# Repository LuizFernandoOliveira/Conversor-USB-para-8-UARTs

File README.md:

# Conversor USB para 8 UARTs

## Descrição
Este circuito eletrônico permite realizar a comunicação serial simutânea de até 8 portas UART com um computador via USB. Esta PCB é ideal para aplicações de testes de comunicação simultânea de múltiplos sensores com um único PC.

---

## Descrições técnicas

- Interface USB: Dispositivo USB High-Speed de 480Mbps;
- Possui oito UARTs (UART0 até UART7) e até 11 pinos de GPIOs controlados via USB;
- Taxa de Transmissão (Baud Rate): Variável de 1200bps até 6Mbps;
- Alimentação Principal: Requer apenas 3.3V;
- Controle de Fluxo: Suporte completo a Hardware Flow Control (CTS e RTS);
- Buffering (FIFO):
  - RX FIFO: 2048 bytes por UART.
  - TX FIFO: 1024 bytes por UART.
- Configurações UART:
  - Bits de Dados: 8 bits;
  - Paridade: Ímpar, Par e Nenhuma;
  - Bits de Parada: 1 ou 2.

---

## Estrutura do repositório
Os arquivos de hardware foram desenvolvidos utilizando o KiCad 9.0.
- **`.kicad_pcb`**: Layout da placa de circuito impresso (Board).
- **`.kicad_sch`**: Esquemático eletrônico do sistema (Schematic).
- **`.kicad_pro`**: Gerenciador de projeto do KiCad (Project).

---

## Autor
**Dr. Luiz Fernando Pinto de Oliveira**

*Engenheiro Eletrônico especializado em Sistemas Embarcados e Ultra-Low Power.*
- **Website:** [FAPLO](https://faplo.webnode.page/)
- **LinkedIn:** [lfpo](https://www.linkedin.com/in/lfpo/)

---

Shield: [![CC BY-NC-ND 4.0][cc-by-nc-nd-shield]][cc-by-nc-nd]

This work is licensed under a
[Creative Commons Attribution-NonCommercial-NoDerivs 4.0 International License][cc-by-nc-nd].

[![CC BY-NC-ND 4.0][cc-by-nc-nd-image]][cc-by-nc-nd]

[cc-by-nc-nd]: http://creativecommons.org/licenses/by-nc-nd/4.0/
[cc-by-nc-nd-image]: https://licensebuttons.net/l/by-nc-nd/4.0/88x31.png
[cc-by-nc-nd-shield]: https://img.shields.io/badge/License-CC%20BY--NC--ND%204.0-lightgrey.svg

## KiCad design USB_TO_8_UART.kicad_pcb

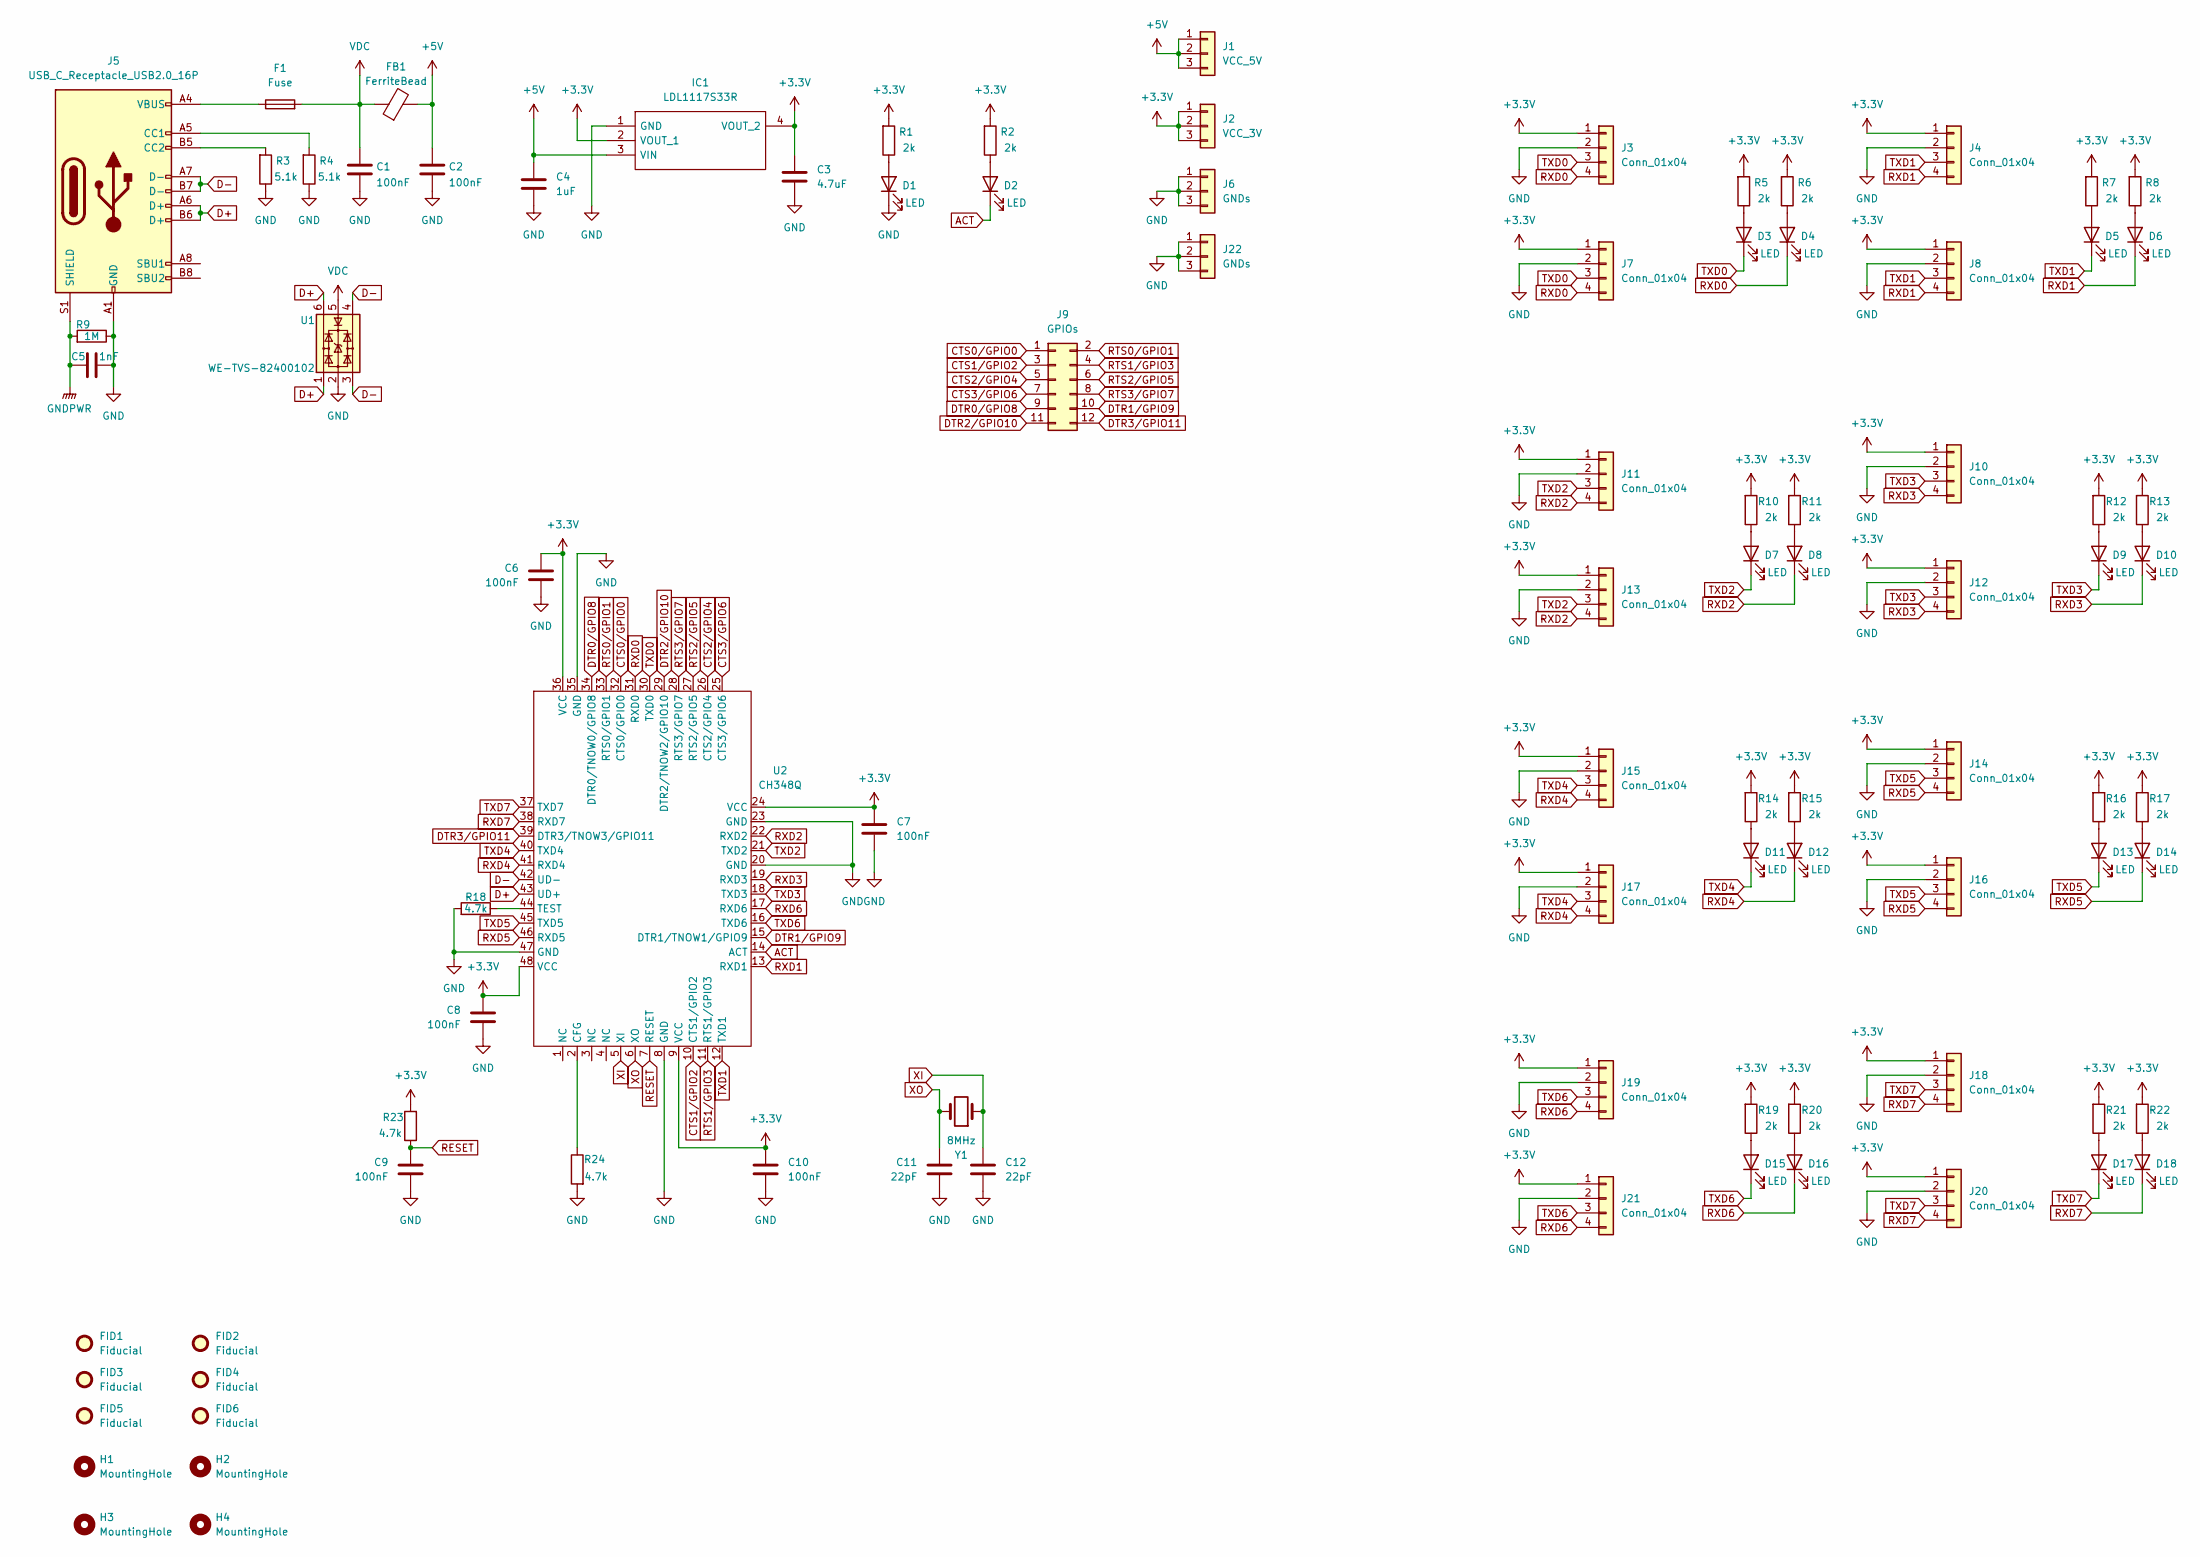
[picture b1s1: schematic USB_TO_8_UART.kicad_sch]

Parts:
C1, C2, C6, C7, C8, C9, C10: 100nF; C_0805_2012Metric
C3: 4.7uF; C_0805_2012Metric
C4: 1uF; C_0805_2012Metric
C5: 1nF; C_0805_2012Metric
C11, C12: 22pF; C_0805_2012Metric
D1, D2, D3, D4, D5, D6, D7, D8, D9, D10, D11, D12, D13, D14, D15, D16, D17, D18: LED; LED_0805_2012Metric
F1: Fuse; Fuse_0805_2012Metric
FB1: FerriteBead; L_0805_2012Metric
FID1, FID2, FID3, FID4, FID5, FID6: Fiducial; Fiducial_1mm_Mask2mm
H1, H2, H3, H4: MountingHole; MountingHole_3.2mm_M3_DIN965
IC1: LDL1117S33R; SOT230P700X180-4N; Manufacturer_Part_Number LDL1117S33R; Mouser Part Number 511-LDL1117S33R
J1: VCC_5V; PinHeader_1x03_P2.54mm_Vertical
J2: VCC_3V; PinHeader_1x03_P2.54mm_Vertical
J3, J4, J10, J11, J14, J15, J18, J19: Conn_01x04; PinHeader_1x04_P2.54mm_Vertical
J5: USB_C_Receptacle_USB2.0_16P; USB_C_Receptacle_HRO_TYPE-C-31-M-12
J6, J22: GNDs; PinHeader_1x03_P2.54mm_Vertical
J7, J8, J12, J13, J16, J17, J20, J21: Conn_01x04; JST_XH_S4B-XH-A_1x04_P2.50mm_Horizontal
J9: GPIOs; PinHeader_2x06_P2.54mm_Vertical
R1, R2, R5, R6, R7, R8, R10, R11, R12, R13, R14, R15, R16, R17, R19, R20, R21, R22: 2k; R_0805_2012Metric
R3, R4: 5.1k; R_0805_2012Metric
R9: 1M; R_0805_2012Metric
R18, R23, R24: 4.7k; R_0805_2012Metric
U1: WE-TVS-82400102; SOT-23-6
U2: CH348Q
Y1: 8MHz; Crystal_SMD_3225-4Pin_3.2x2.5mm

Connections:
+3.3V: C3.1, C6.1, C7.1, C8.1, C10.1, IC1.2 (VOUT_1), IC1.4 (VOUT_2), J2.1, J2.2, J2.3, J3.1, J4.1, J7.1, J8.1, J10.1, J11.1, J12.1, J13.1, J14.1, J15.1, J16.1, J17.1, J18.1, J19.1, J20.1, J21.1, R1.2, R2.2, R5.2, R6.2, R7.2, R8.2, R10.2, R11.2, R12.2, R13.2, R14.2, R15.2, R16.2, R17.2, R19.2, R20.2, R21.2, R22.2, R23.2, U2.9 (VCC), U2.24 (VCC), U2.36 (VCC), U2.48 (VCC)
+5V: C2.1, C4.1, FB1.2, IC1.3 (VIN), J1.1, J1.2, J1.3
ACT: D2.1 (K), U2.14 (ACT)
CTS0/GPIO0: J9.1, U2.32 (CTS0/GPIO0)
CTS1/GPIO2: J9.3, U2.10 (CTS1/GPIO2)
CTS2/GPIO4: J9.5, U2.26 (CTS2/GPIO4)
CTS3/GPIO6: J9.7, U2.25 (CTS3/GPIO6)
D+: J5.A6 (D+), J5.B6 (D+), U1.1, U1.6, U2.43 (UD+)
D-: J5.A7 (D-), J5.B7 (D-), U1.3, U1.4, U2.42 (UD-)
DTR0/GPIO8: J9.9, U2.34 (DTR0/TNOW0/GPIO8)
DTR1/GPIO9: J9.10, U2.15 (DTR1/TNOW1/GPIO9)
DTR2/GPIO10: J9.11, U2.29 (DTR2/TNOW2/GPIO10)
DTR3/GPIO11: J9.12, U2.39 (DTR3/TNOW3/GPIO11)
GND: C1.2, C2.2, C3.2, C4.2, C5.2, C6.2, C7.2, C8.2, C9.2, C10.2, C11.2, C12.2, D1.1 (K), IC1.1 (GND), J3.2, J4.2, J5.A1 (GND), J5.A12 (GND), J5.B1 (GND), J5.B12 (GND), J6.1, J6.2, J6.3, J7.2, J8.2, J10.2, J11.2, J12.2, J13.2, J14.2, J15.2, J16.2, J17.2, J18.2, J19.2, J20.2, J21.2, J22.1, J22.2, J22.3, R3.1, R4.1, R9.1, R18.2, R24.2, U1.2, U2.8 (GND), U2.20 (GND), U2.23 (GND), U2.35 (GND), U2.47 (GND)
GNDPWR: C5.1, J5.S1 (SHIELD), R9.2
unnamed: D1.2 (A), R1.1
unnamed: D2.2 (A), R2.1
unnamed: D3.2 (A), R5.1
unnamed: D4.2 (A), R6.1
unnamed: D5.2 (A), R7.1
unnamed: D6.2 (A), R8.1
unnamed: D7.2 (A), R10.1
unnamed: D8.2 (A), R11.1
unnamed: D9.2 (A), R12.1
unnamed: D10.2 (A), R13.1
unnamed: D11.2 (A), R14.1
unnamed: D12.2 (A), R15.1
unnamed: D13.2 (A), R16.1
unnamed: D14.2 (A), R17.1
unnamed: D15.2 (A), R19.1
unnamed: D16.2 (A), R20.1
unnamed: D17.2 (A), R21.1
unnamed: D18.2 (A), R22.1
unnamed: F1.1, J5.A4 (VBUS), J5.A9 (VBUS), J5.B4 (VBUS), J5.B9 (VBUS)
unnamed: J5.A5 (CC1), R4.2
unnamed: J5.B5 (CC2), R3.2
unnamed: R24.1, U2.2 (CFG)
unnamed: R18.1, U2.44 (TEST)
RESET: C9.1, R23.1, U2.7 (RESET)
RTS0/GPIO1: J9.2, U2.33 (RTS0/GPIO1)
RTS1/GPIO3: J9.4, U2.11 (RTS1/GPIO3)
RTS2/GPIO5: J9.6, U2.27 (RTS2/GPIO5)
RTS3/GPIO7: J9.8, U2.28 (RTS3/GPIO7)
RXD0: D4.1 (K), J3.4, J7.4, U2.31 (RXD0)
RXD1: D6.1 (K), J4.4, J8.4, U2.13 (RXD1)
RXD2: D8.1 (K), J11.4, J13.4, U2.22 (RXD2)
RXD3: D10.1 (K), J10.4, J12.4, U2.19 (RXD3)
RXD4: D12.1 (K), J15.4, J17.4, U2.41 (RXD4)
RXD5: D14.1 (K), J14.4, J16.4, U2.46 (RXD5)
RXD6: D16.1 (K), J19.4, J21.4, U2.17 (RXD6)
RXD7: D18.1 (K), J18.4, J20.4, U2.38 (RXD7)
TXD0: D3.1 (K), J3.3, J7.3, U2.30 (TXD0)
TXD1: D5.1 (K), J4.3, J8.3, U2.12 (TXD1)
TXD2: D7.1 (K), J11.3, J13.3, U2.21 (TXD2)
TXD3: D9.1 (K), J10.3, J12.3, U2.18 (TXD3)
TXD4: D11.1 (K), J15.3, J17.3, U2.40 (TXD4)
TXD5: D13.1 (K), J14.3, J16.3, U2.45 (TXD5)
TXD6: D15.1 (K), J19.3, J21.3, U2.16 (TXD6)
TXD7: D17.1 (K), J18.3, J20.3, U2.37 (TXD7)
VDC: C1.1, F1.2, FB1.1, U1.5
XI: C12.1, U2.5 (XI), Y1.1
XO: C11.1, U2.6 (XO), Y1.2

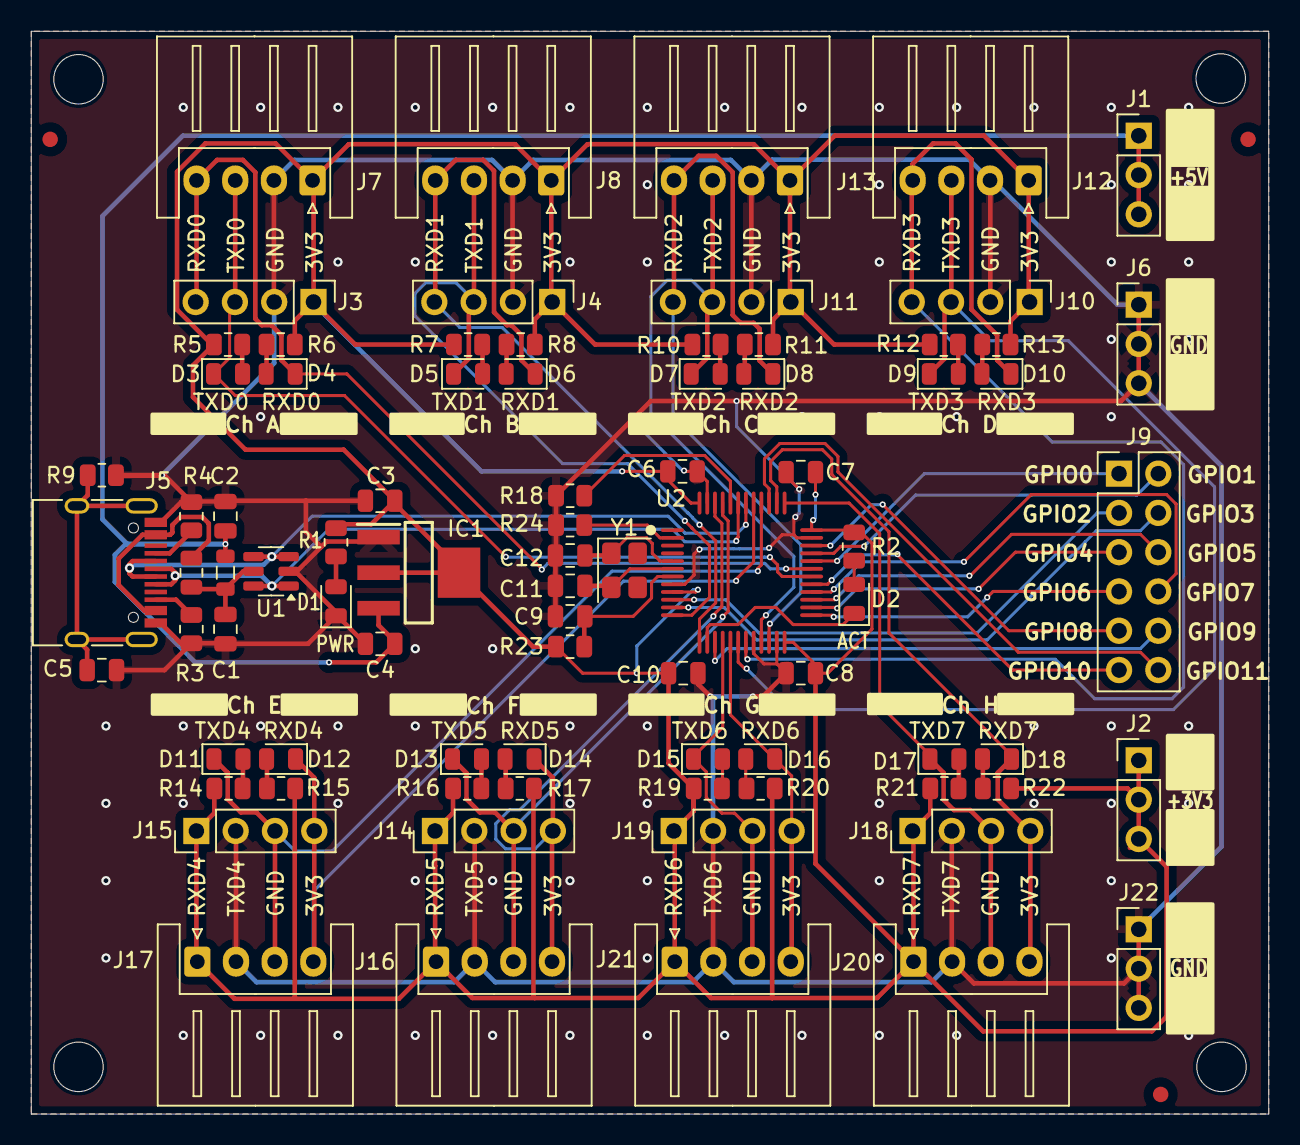
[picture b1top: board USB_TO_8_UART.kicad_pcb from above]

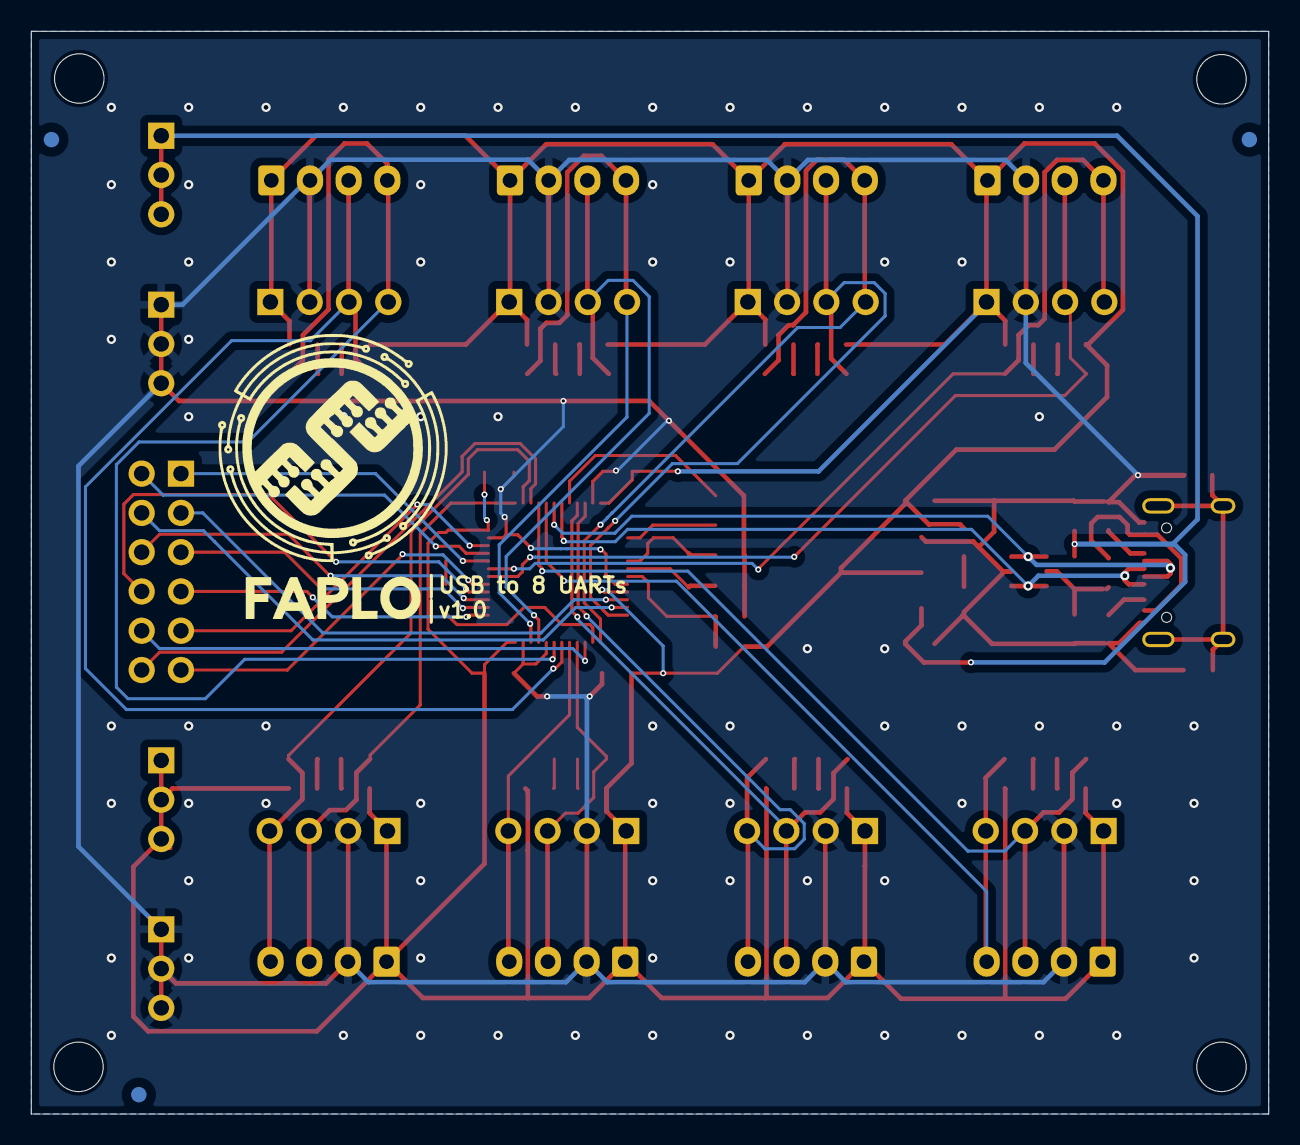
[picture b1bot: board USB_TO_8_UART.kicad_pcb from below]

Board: 2 copper layers, 80.0 x 70.0 mm, 92 parts (3 on the bottom side), 62 nets.

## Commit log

2026-04-17 Inicialização de repositório
2026-04-17 Enhance README with project details and author info
    Added project status, technical descriptions, repository structure, and author information to README.
2026-04-17 Add LICENSE file with CC BY-NC-ND 4.0 License
    Added Creative Commons Attribution-NonCommercial-NoDerivatives 4.0 International Public License to the project.
